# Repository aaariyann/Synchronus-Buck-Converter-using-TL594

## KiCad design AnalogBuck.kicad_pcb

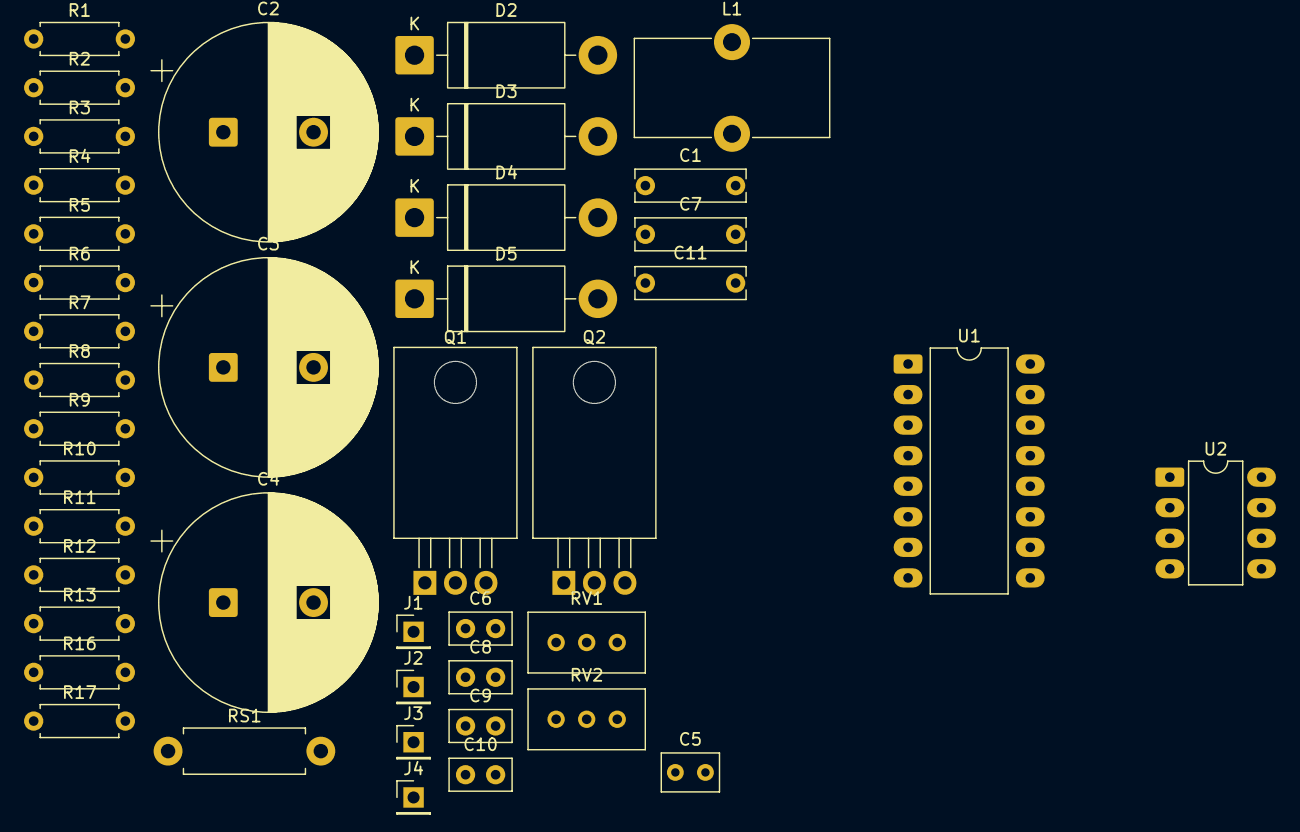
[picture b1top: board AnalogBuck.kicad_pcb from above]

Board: 2 copper layers, 42 parts (0 on the bottom side), 24 nets, no tracks yet.

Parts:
C1, C7, C11: 1uF; C_Rect_L9.0mm_W2.5mm_P7.50mm_MKT
C2, C3, C4: 470uF; CP_Radial_D18.0mm_P7.50mm
C5: 1.5nF; C_Rect_L4.6mm_W3.0mm_P2.50mm_MKS02_FKP02
C6, C8, C9, C10: 100nF; C_Disc_D5.0mm_W2.5mm_P2.50mm
D2, D3, D4, D5: 1N5822; D_DO-201AD_P15.24mm_Horizontal
J1, J2, J3, J4: Conn_01x01_Pin; PinHeader_1x01_P2.54mm_Vertical
L1: 100uH; L_Toroid_Vertical_L16.0mm_W8.0mm_P7.62mm
Q1, Q2: IRFZ44N; TO-220-3_Horizontal_TabDown
R1: 2.2K; R_Axial_DIN0207_L6.3mm_D2.5mm_P7.62mm_Horizontal
R2, R3: 10R; R_Axial_DIN0207_L6.3mm_D2.5mm_P7.62mm_Horizontal
R4, R5, R7, R8: 10K; R_Axial_DIN0207_L6.3mm_D2.5mm_P7.62mm_Horizontal
R6: 6.8K; R_Axial_DIN0207_L6.3mm_D2.5mm_P7.62mm_Horizontal
R9: 33K; R_Axial_DIN0207_L6.3mm_D2.5mm_P7.62mm_Horizontal
R10, R11, R16: 1.5K; R_Axial_DIN0207_L6.3mm_D2.5mm_P7.62mm_Horizontal
R12, R13: 15K; R_Axial_DIN0207_L6.3mm_D2.5mm_P7.62mm_Horizontal
R17: 470R; R_Axial_DIN0207_L6.3mm_D2.5mm_P7.62mm_Horizontal
RS1: 0.01R; R_Axial_DIN0411_L9.9mm_D3.6mm_P12.70mm_Horizontal
RV1: 10K; Potentiometer_Bourns_3296W_Vertical
RV2: 1K; Potentiometer_Bourns_3296W_Vertical
U1: TL594; DIP-16_W10.16mm_LongPads
U2: IR2104; DIP-8_W7.62mm_LongPads

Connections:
/VOUT+: C2.1, C10.1, J1.1 (Pin_1_1), L1.2, RV1.1, RV1.2
/VOUT-: J2.1 (Pin_1_1), R16.2, RS1.1
/VREF: C6.1, C7.1, R9.1, R13.1, U1.14 (REF)
GND: C2.2, C3.2, C4.2, C5.2, C6.2, D5.2 (A), J4.1 (Pin_1_1), Q2.3 (S), R1.2, R5.2, R6.2, R7.2, R8.2, R10.2, RS1.2, RV2.3, U1.7 (GND), U1.13 (OUTCTRL), U2.4 (COM)
unnamed: C9.2, R12.2
unnamed: C8.1, C10.2
unnamed: C1.1, D2.1 (K), U2.8 (VB)
unnamed: D3.2 (A), Q1.1 (G), R2.1, R4.1
unnamed: D3.1 (K), D5.1 (K), L1.1, Q1.3 (S), Q2.2 (D), R2.2, R4.2, U2.7 (HO)
unnamed: D4.2 (A), Q2.1 (G), R3.1, R5.1
unnamed: D4.1 (K), R3.2, U2.5 (LO)
unnamed: R11.2, RV1.3
unnamed: R13.2, R17.2, RV2.1, RV2.2
unnamed: C8.2, R10.1, R11.1, U1.1 (1IN+)
unnamed: C9.1, R8.1, R9.2, U1.2 (1IN-)
unnamed: R16.1, U1.16 (2IN+)
unnamed: C11.1, R17.1, U1.15 (2IN-)
unnamed: C5.1, U1.5 (CT)
unnamed: C7.2, R7.1, U1.4 (DTC)
unnamed: R1.1, U1.9 (E1), U1.10 (E2), U2.2 (IN)
unnamed: C11.2, R12.1, U1.3 (FB)
unnamed: R6.1, U1.6 (RT)
unnamed: C1.2, U2.6 (VS)
VCC: C3.1, C4.1, D2.2 (A), J3.1 (Pin_1_1), Q1.2 (D), U1.8 (C1), U1.11 (C2), U1.12 (VCC), U2.1 (VCC), U2.3 (~SD)
